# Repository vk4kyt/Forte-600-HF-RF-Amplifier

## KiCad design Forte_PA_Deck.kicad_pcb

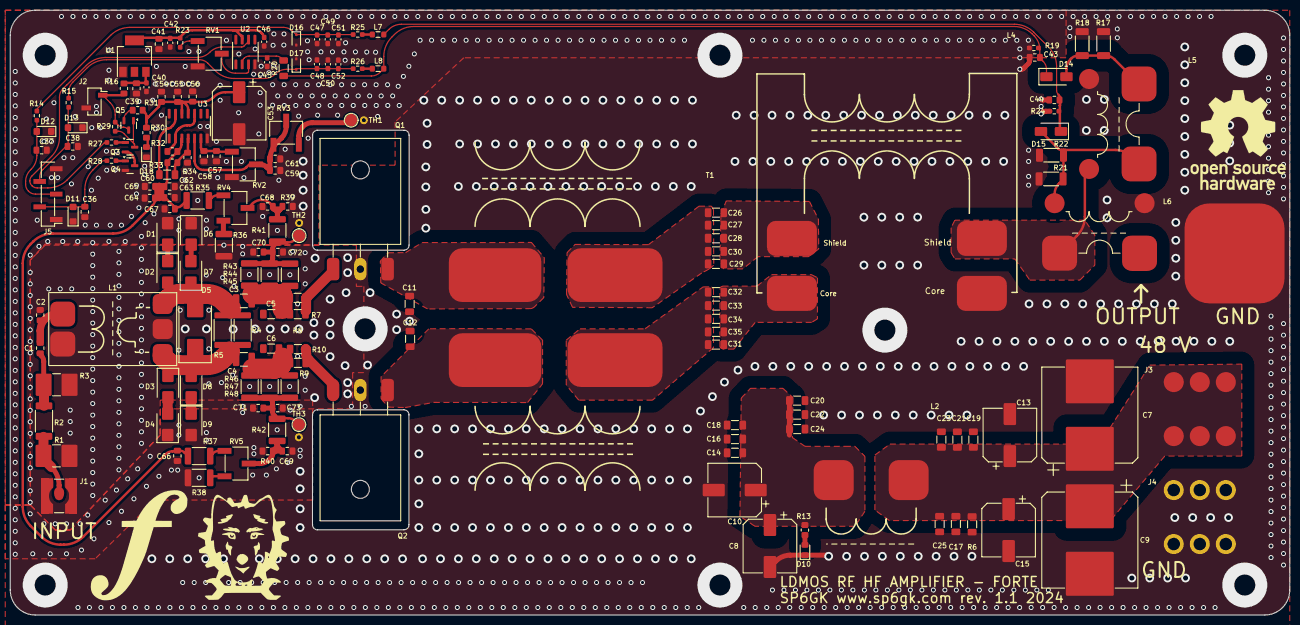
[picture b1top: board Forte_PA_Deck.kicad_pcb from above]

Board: 2 copper layers, 256.0 x 121.0 mm, 167 parts (0 on the bottom side), 65 nets.

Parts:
C1: 33n; C_0805_2012Metric_Pad1.18x1.45mm_HandSolder
C2: 22p; C_0805_2012Metric_Pad1.18x1.45mm_HandSolder
C3, C4: 100n; C_1210_3225Metric_Pad1.33x2.70mm_HandSolder
C5, C6, C14, C16, C18, C19, C21, C29: 100n; C_1206_3216Metric_Pad1.33x1.80mm_HandSolder
C7, C9: 330u; CP_Elec_18x17.5
C8, C13: 33u; CP_Elec_10x10.5
C10, C15: 10u; CP_Elec_10x10.5
C11, C12, C60: 100p; C_1206_3216Metric_Pad1.33x1.80mm_HandSolder
C17: 1u; C_1206_3216Metric_Pad1.33x1.80mm_HandSolder
C20, C22, C23, C26, C27, C28, C30, C31, C32, C33, C34, C35: 22n; C_1206_3216Metric_Pad1.33x1.80mm_HandSolder
C24, C25: 10n; C_1206_3216Metric_Pad1.33x1.80mm_HandSolder
C36, C37, C38, C43, C44, C56, C58, C61, C65, C66, C67, C68, C69, C72, C73: 100n; C_0805_2012Metric_Pad1.18x1.45mm_HandSolder
C39, C41, C54, C57, C59, C62, C63: 10u; C_0805_2012Metric_Pad1.18x1.45mm_HandSolder
C40, C42, C45, C46, C49, C50: 100n; C_0603_1608Metric_Pad1.08x0.95mm_HandSolder
C47, C48: 1u; C_0603_1608Metric_Pad1.08x0.95mm_HandSolder
C51, C52: 10n; C_0603_1608Metric_Pad1.08x0.95mm_HandSolder
C53: 47u; CP_Elec_10x10.5
C55, C64, C70, C71: 1u; C_0805_2012Metric_Pad1.18x1.45mm_HandSolder
D1, D4, D6, D9: 1N4148WT; D_SMB
D2, D3, D7, D8: 4.7; D_SMB
D5: D_TVS; D_SMC_Handsoldering
D10: 48V_LED; LED_0805_2012Metric_Pad1.15x1.40mm_HandSolder
D11: 3.6; D_SMF
D12, D13: Protection TVS 5V; D_SMF
D14, D15: 1N4148W; D_SMA
D16, D17: SD12_SOD323; D_SOD-323
D18: BIAS_LED; LED_0805_2012Metric_Pad1.15x1.40mm_HandSolder
J1: SMA; SMA_Amphenol_132134-10_Vertical
J2: 5.08mm; PinSocket_1x02_P2.54mm_Vertical_SMD_Pin1Right
J3, J4: Keystone M5; M5_screw_terminal_Keystone
J5: Conn_01x05; PinHeader_1x05_P2.54mm_Vertical_SMD_Pin1Left
J6: Conn_Coaxial; Coax_connector
L1: 4:1; Binocular_trafo_small
L2: 12 uH 20 A; EMI_inductor
L4: 2x mat 43. 4T RG174 50 Ohm; Trafo_623-2661102002
L5: FT50-61 30T 1T RG-142 coax; FT82_trafo
L6: FT82-61 30T 1T-RG213 coax; FT82_trafo
L7, L8: 100u; L_0805_2012Metric_Pad1.05x1.20mm_HandSolder
Q1: MRF300AN; TO-247-3_Horizontal_TabDown
Q2: MRF300BN; TO-247-3_Horizontal_TabDown
Q3, Q4: BC846; SOT-23
Q5: AO3400A; SOT-23
R1, R3: 300; R_2816_7142Metric_Pad3.20x4.45mm_HandSolder
R2: 18; R_2512_6332Metric_Pad1.40x3.35mm_HandSolder
R4, R5: 33; R_2512_6332Metric
R6: 47k; C_1206_3216Metric_Pad1.33x1.80mm_HandSolder
R7, R8, R9, R10: 4.7; C_1206_3216Metric_Pad1.33x1.80mm_HandSolder
R13: x; R_0805_2012Metric_Pad1.20x1.40mm_HandSolder
R14, R15, R25, R26: 100; R_0603_1608Metric_Pad0.98x0.95mm_HandSolder
R16, R31, R32: 10; R_0805_2012Metric_Pad1.20x1.40mm_HandSolder
R17, R18, R21, R22: 100; R_2010_5025Metric_Pad1.40x2.65mm_HandSolder
R19, R24, R29: 10k; R_0603_1608Metric_Pad0.98x0.95mm_HandSolder
R20: 10k; R_1206_3216Metric_Pad1.30x1.75mm_HandSolder
R23, R27, R28: 1k; R_0603_1608Metric_Pad0.98x0.95mm_HandSolder
R30: 470; R_0805_2012Metric_Pad1.20x1.40mm_HandSolder
R33: 2.2k; R_0805_2012Metric_Pad1.20x1.40mm_HandSolder
R34: 14k; R_0805_2012Metric_Pad1.20x1.40mm_HandSolder
R35, R36, R37, R38, R41, R42, R43, R44, R45, R46, R47, R48: 100; R_1812_4532Metric_Pad1.30x3.40mm_HandSolder
R39, R40: 4.7k; C_0805_2012Metric_Pad1.18x1.45mm_HandSolder
RV1, RV2, RV3: 10k; Potentiometer_Bourns_3269W_Vertical
RV4, RV5: 500; Potentiometer_Bourns_3269W_Vertical
T1: Transformer_1P_1S; TLT_Trafo
TH1, TH2, TH3: 5k; R_Axial_DIN0207_L6.3mm_D2.5mm_P2.54mm_Vertical
U1: AMS1117-5.0; SOT-223-3_TabPin2
U2: OP07; SOIC-8_3.9x4.9mm_P1.27mm
U3: LM723_DIP14; SO-14_3.9x8.65mm_P1.27mm

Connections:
48V_IN: C7.1, C9.1, C13.1, C15.1, C17.1, C19.1, C21.1, C23.1, C25.1, J3.1, L2.1, R6.1
+5V: C41.1, C42.1, C46.1, R23.1, U1.2 (VO), U2.7 (V+)
+12V: J2.1, Q5.3 (D), R16.1, R29.1
+48V: C8.1, C10.1, C14.1, C16.1, C18.1, C20.1, C22.1, C24.1, L2.2, R13.1
/AMOS_D: C11.2, Q1.3 (D), T1.1 (AA)
/ATLT_OUT: C26.1, C27.1, C28.1, C29.1, C30.1, T1.2
/BMOS_D: C12.1, Q2.1 (D), T1.3
/BTLT_OUT: C31.1, C32.1, C33.1, C34.1, C35.1, T1.4
/Bias_regulation/A_MOS_G: C3.2, C5.1, R7.1, R8.1, R43.2, R44.2, R45.2
/Bias_regulation/B_MOS_G: C4.2, C6.1, R9.1, R10.1, R46.2, R47.2, R48.2
/Bias_regulation/Bias_DC_IN: C53.1, C54.1, C55.1, C56.1, R30.1, R31.2, U3.11 (VC), U3.12 (V+)
/Bias_regulation/Bias_EN: C36.1, D11.2 (A2), J5.2, R28.1
/Bias_regulation/Bias_Voltage: C62.1, C63.1, C64.1, C65.1, C66.1, C67.1, R32.2, R33.1, R35.1, R37.1, U3.3 (CSEN)
/Bias_regulation/~HIGH_SWR: R27.1, U2.6
/SWR_Meter/FWD_PWR: C47.1, C49.1, C51.1, D16.1 (A1), R14.1, R25.1
/SWR_Meter/IN: L4.1, L5.4, L6.1
/SWR_Meter/OUT: J6.1 (In), L6.2
/SWR_Meter/REF_PWR: C48.1, C50.1, C52.1, D17.1 (A1), R15.1, R26.1
/To_GateA: C3.1, D2.2 (A), D5.2 (A2), D7.1 (K), L1.3, R4.1, R5.1
/To_GateB: C4.1, D3.1 (K), D5.1 (A1), D8.2 (A), L1.4, R4.2, R5.2
GND: C2.1, C7.2, C8.2, C9.2, C10.2, C11.1, C12.2, C13.2, C14.2, C15.2, C16.2, C17.2, C18.2, C19.2, C20.2, C21.2, C22.2, C23.2, C24.2, C25.2, C36.2, C37.2, C38.2, C39.2, C40.2, C41.2, C42.2, C43.2, C44.2, C45.2, C46.2, C47.2, C48.2, C49.2, C50.2, C51.2, C52.2, C53.2, C54.2, C55.2, C56.2, C57.2, C58.2, C59.2, C61.2, C62.2, C63.2, C64.2, C65.2, C66.2, C67.2, C68.2, C69.2, C70.2, C71.2, C72.2, C73.2, D1.2 (A), D4.1 (K), D6.1 (K), D9.2 (A), D10.1 (K), D11.1 (A1), D12.1 (A1), D13.1 (A1), D16.2 (A2), D17.2 (A2), D18.1 (K), J1.2 (Ext), J2.2, J4.1, J5.1, J5.5, J6.2 (Ext), L1.1, L4.3, L5.3, L6.3, Q1.2 (S), Q2.2 (S), Q4.2 (E), R1.2, R3.2, R6.2, R17.1, R18.1, R19.2, R21.2, R22.2, R24.2, R34.2, R36.2, R38.2, R39.2, R40.2, RV1.3, RV2.3, TH1.2, TH2.2, TH3.2, U1.1 (GND), U2.4 (V-), U3.7 (V-)
unnamed: C1.1, R2.2, R3.1
unnamed: C1.2, C2.2, L1.2
unnamed: C26.2, C27.2, C28.2, C29.2, C30.2, L4.2
unnamed: C31.2, C32.2, C33.2, C34.2, C35.2, L4.4
unnamed: C68.1, R39.1, R41.1, RV4.2
unnamed: C69.1, R40.1, R42.1, RV5.2
unnamed: C70.1, C72.1, R41.2, R43.1, R44.1, R45.1, TH2.1
unnamed: C71.1, C73.1, R42.2, R46.1, R47.1, R48.1, TH3.1
unnamed: D1.1 (K), D2.1 (K)
unnamed: D3.2 (A), D4.2 (A)
unnamed: D6.2 (A), D7.2 (A)
unnamed: D8.1 (K), D9.1 (K)
unnamed: D10.2 (A), R13.2
unnamed: C37.1, D12.2 (A2), J5.3, R14.2
unnamed: C38.1, D13.2 (A2), J5.4, R15.2
unnamed: D14.2 (A), L5.2, R17.2, R18.2
unnamed: C43.1, D14.1 (K), L8.1, R19.1, R20.1
unnamed: D15.2 (A), L5.1, L6.4, R21.1, R22.1
unnamed: C44.1, D15.1 (K), L7.1, R24.1
unnamed: D18.2 (A), R30.2
unnamed: J1.1 (In), R1.1, R2.1
unnamed: L7.2, R25.2
unnamed: L8.2, R26.2
unnamed: Q1.1 (G), R7.2, R8.2
unnamed: Q2.3 (G), R9.2, R10.2
unnamed: Q3.1 (B), R27.2
unnamed: Q3.3 (C), Q5.1 (G), R29.2
unnamed: Q3.2 (E), Q4.3 (C)
unnamed: Q4.1 (B), R28.2
unnamed: Q5.2 (S), R31.1
unnamed: R23.2, RV1.1
unnamed: R35.2, RV4.1
unnamed: R36.1, RV4.3
unnamed: R37.2, RV5.1
unnamed: R38.1, RV5.3
unnamed: RV3.3, TH1.1
unnamed: C39.1, C40.1, R16.2, U1.3 (VI)
unnamed: RV1.2, U2.3 (+)
unnamed: C45.1, R20.2, U2.2 (-)
unnamed: C59.1, C61.1, RV2.2, RV3.1, RV3.2, U3.5 (+)
unnamed: C60.2, R33.2, R34.1, U3.4 (-)
unnamed: C60.1, U3.13 (FC)
unnamed: R32.1, U3.2 (ILIM), U3.10 (Vout)
unnamed: C57.1, C58.1, RV2.1, U3.6 (VREF)

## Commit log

2024-08-17 Forte 600 project documentation, and manuals
    The documentation contains measurements, an in depth description of design decisions, and the theory of operation.
2024-08-17 Rename Forte_PA_Deck.pdf to Forte_PA_Deck_Schematic.pdf
2024-09-01 Add files via upload
    Fixed DRC shorted nets error
2024-09-10 Used ERC on PA-Deck Schematic
    Initially many hundreds of warnings, and some errors.
    Apart from 8 exclusions These have all largely been fixed.
    Many Symbols required updating from the appropriate library, but mostly a huge number or warnings about "symbol pin or wire end off grid connection". Took a while, but I figured out what the problem 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
    L5 & L6 exclusion referred to a TXRX library that wasn't available.
2024-09-14 Ready to Order
    Applied minor changes in preparation to order CPBs and components.
